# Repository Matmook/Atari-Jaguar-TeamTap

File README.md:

# Atari-Jaguar-TeamTap

This is an attempt to recreate the Atari Jaguar TeamTap schematic.

There is a catch on the original PCB: 
- the 5v from the Jaguar powers TeamTap's internal logic (74HC154 and 74HC244).
- pad's pin 7 is supposed to be used to power the pad's logic (74HC244).
- but all pads pin 7 are left floating in the TeamTam..
I guess that's some Atari magic => the pad's 74HC244 is fed by the other IOs, not VCC.
There is a "Magic" shunt on my pcb to test the pads behaviour when fed with 5v (as it should).

Matthieu Barreteau (Matmook) 2024

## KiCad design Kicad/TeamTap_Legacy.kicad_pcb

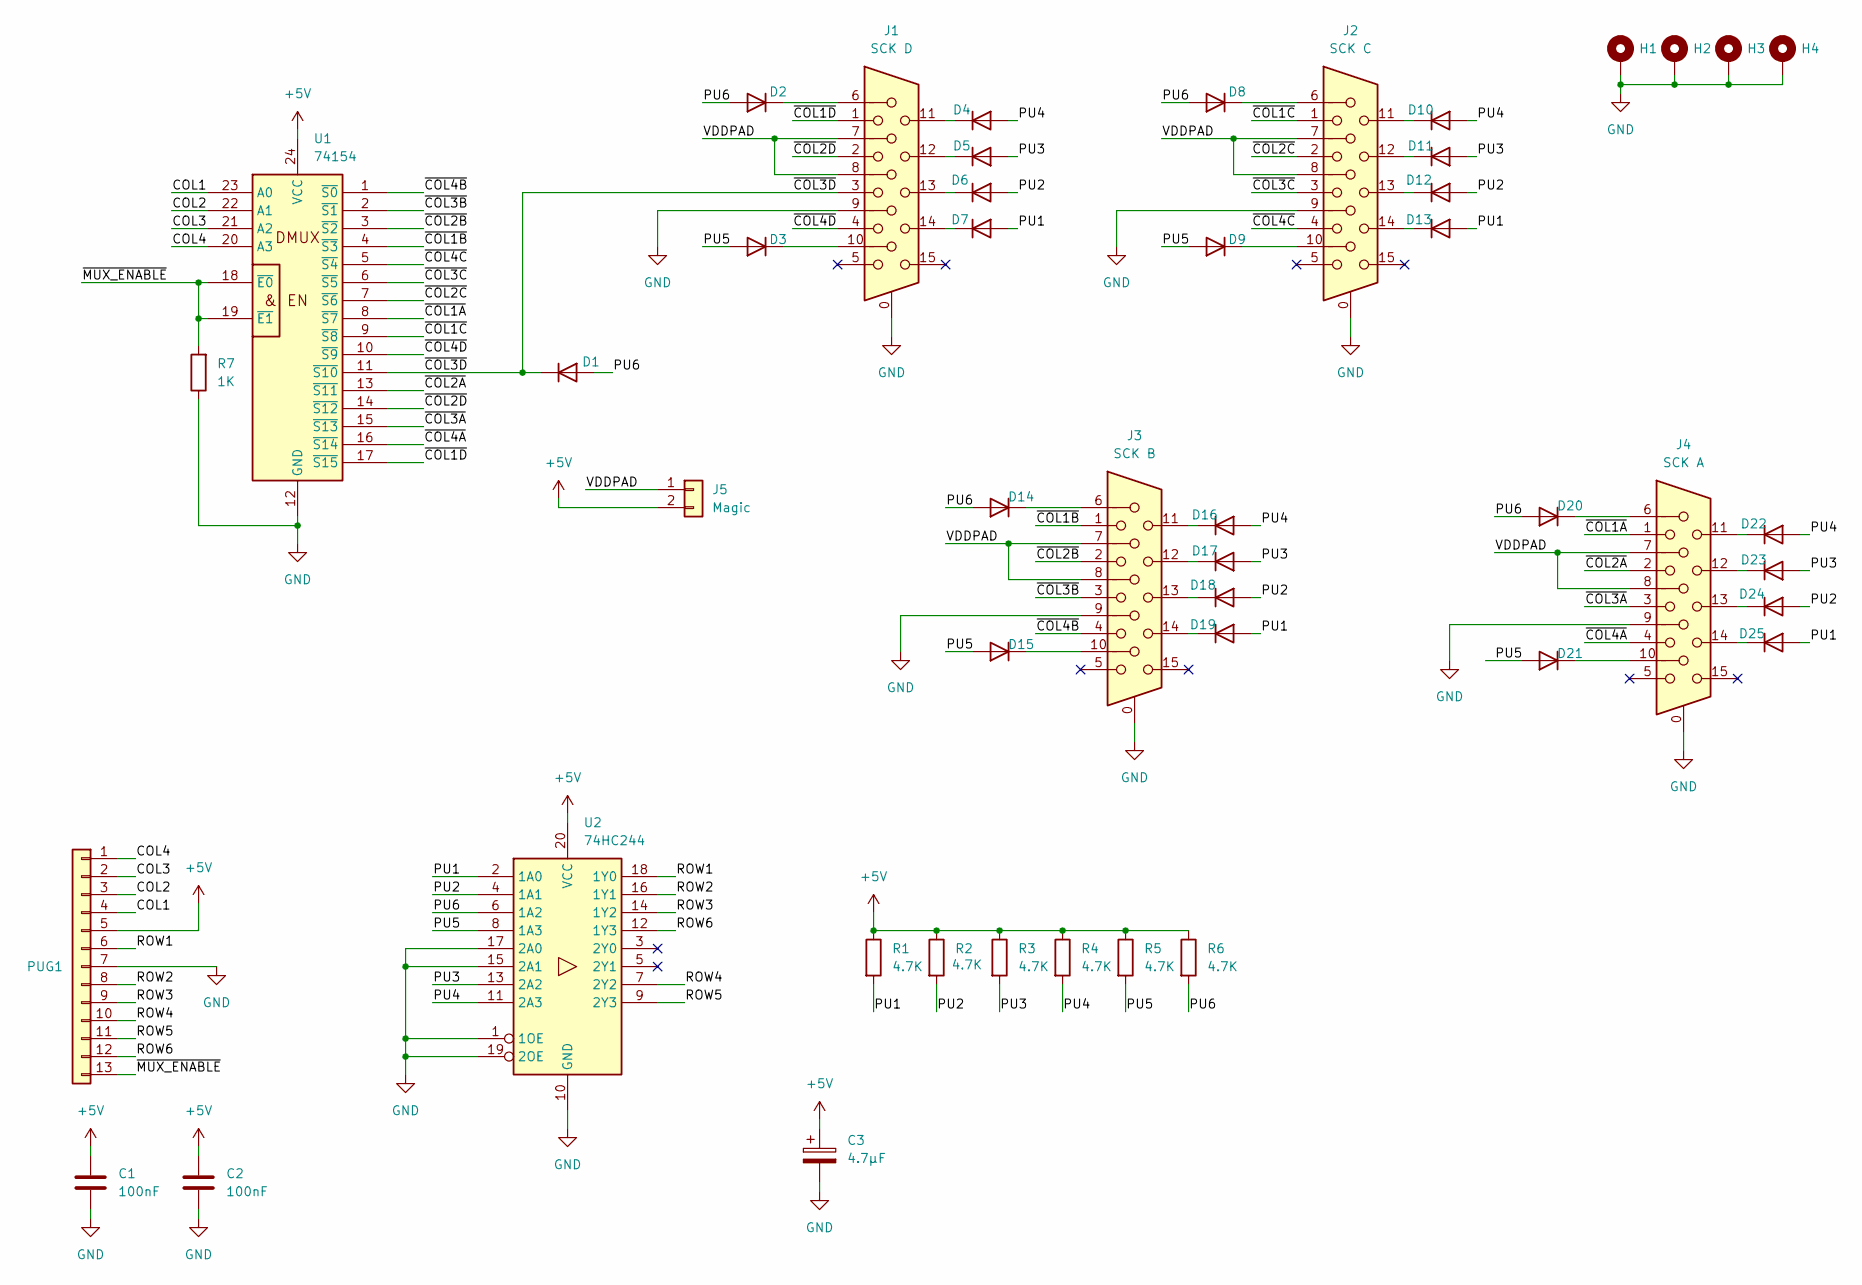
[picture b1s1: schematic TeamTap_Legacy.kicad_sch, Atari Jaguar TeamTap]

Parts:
C1, C2: 100nF; C_0603_1608Metric_Pad1.08x0.95mm_HandSolder
C3: 4.7µF; CP_Radial_D5.0mm_P2.50mm
D1, D2, D3, D4, D5, D6, D7, D8, D9, D10, D11, D12, D13, D14, D15, D16, D17, D18, D19, D20, D21, D22, D23, D24, D25: D; D_SOD-123
H1, H2, H3, H4: MountingHole_Pad; MountingHole_5mm_Pad_TopBottom
J1: SCK D; DSUB-15-HD_Male_Horizontal_P2.29x1.98mm_EdgePinOffset3.03mm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
J2: SCK C; DSUB-15-HD_Male_Horizontal_P2.29x1.98mm_EdgePinOffset3.03mm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
J3: SCK B; DSUB-15-HD_Male_Horizontal_P2.29x1.98mm_EdgePinOffset3.03mm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
J4: SCK A; DSUB-15-HD_Male_Horizontal_P2.29x1.98mm_EdgePinOffset3.03mm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
J5: Magic; PinHeader_1x02_P2.54mm_Vertical
PUG1: Conn_01x13; PinHeader_1x13_P2.54mm_Vertical
R1, R2, R3, R4, R5, R6: 4.7K; R_0603_1608Metric_Pad0.98x0.95mm_HandSolder
R7: 1K; R_0603_1608Metric_Pad0.98x0.95mm_HandSolder
U1: 74154; SOIC-24W_7.5x15.4mm_P1.27mm
U2: 74HC244; SOIC-20W_7.5x12.8mm_P1.27mm

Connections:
+5V: C1.1, C2.1, C3.1, J5.2, PUG1.5, R1.1, R2.1, R3.1, R4.1, R5.1, R6.1, U1.24 (VCC), U2.20 (VCC)
/COL1: PUG1.4, U1.23 (A0)
/COL2: PUG1.3, U1.22 (A1)
/COL3: PUG1.2, U1.21 (A2)
/COL4: PUG1.1, U1.20 (A3)
/PU1: D7.2 (A), D13.2 (A), D19.2 (A), D25.2 (A), R1.2, U2.2 (1A0)
/PU2: D6.2 (A), D12.2 (A), D18.2 (A), D24.2 (A), R2.2, U2.4 (1A1)
/PU3: D5.2 (A), D11.2 (A), D17.2 (A), D23.2 (A), R3.2, U2.13 (2A2)
/PU4: D4.2 (A), D10.2 (A), D16.2 (A), D22.2 (A), R4.2, U2.11 (2A3)
/PU5: D3.2 (A), D9.2 (A), D15.2 (A), D21.2 (A), R5.2, U2.8 (1A3)
/PU6: D1.2 (A), D2.2 (A), D8.2 (A), D14.2 (A), D20.2 (A), R6.2, U2.6 (1A2)
/ROW1: PUG1.6, U2.18 (1Y0)
/ROW2: PUG1.8, U2.16 (1Y1)
/ROW3: PUG1.9, U2.14 (1Y2)
/ROW4: PUG1.10, U2.7 (2Y2)
/ROW5: PUG1.11, U2.9 (2Y3)
/ROW6: PUG1.12, U2.12 (1Y3)
/VDDPAD: J1.7, J1.8, J2.7, J2.8, J3.7, J3.8, J4.7, J4.8, J5.1
/~COL1A: J4.1, U1.8 (~S7)
/~COL1B: J3.1, U1.4 (~S3)
/~COL1C: J2.1, U1.9 (~S8)
/~COL1D: J1.1, U1.17 (~S15)
/~COL2A: J4.2, U1.13 (~S11)
/~COL2B: J3.2, U1.3 (~S2)
/~COL2C: J2.2, U1.7 (~S6)
/~COL2D: J1.2, U1.14 (~S12)
/~COL3A: J4.3, U1.15 (~S13)
/~COL3B: J3.3, U1.2 (~S1)
/~COL3C: J2.3, U1.6 (~S5)
/~COL3D: D1.1 (K), J1.3, U1.11 (~S10)
/~COL4A: J4.4, U1.16 (~S14)
/~COL4B: J3.4, U1.1 (~S0)
/~COL4C: J2.4, U1.5 (~S4)
/~COL4D: J1.4, U1.10 (~S9)
/~MUX_ENABLE: PUG1.13, R7.2, U1.18 (~E0), U1.19 (~E1)
GND: C1.2, C2.2, C3.2, H1.1, H2.1, H3.1, H4.1, J1.0, J1.9, J2.0, J2.9, J3.0, J3.9, J4.0, J4.9, PUG1.7, R7.1, U1.12 (GND), U2.1 (1OE), U2.10 (GND), U2.15 (2A1), U2.17 (2A0), U2.19 (2OE)
unnamed: D2.1 (K), J1.6
unnamed: D3.1 (K), J1.10
unnamed: D4.1 (K), J1.11
unnamed: D5.1 (K), J1.12
unnamed: D6.1 (K), J1.13
unnamed: D7.1 (K), J1.14
unnamed: D8.1 (K), J2.6
unnamed: D9.1 (K), J2.10
unnamed: D10.1 (K), J2.11
unnamed: D11.1 (K), J2.12
unnamed: D12.1 (K), J2.13
unnamed: D13.1 (K), J2.14
unnamed: D14.1 (K), J3.6
unnamed: D15.1 (K), J3.10
unnamed: D16.1 (K), J3.11
unnamed: D17.1 (K), J3.12
unnamed: D18.1 (K), J3.13
unnamed: D19.1 (K), J3.14
unnamed: D20.1 (K), J4.6
unnamed: D21.1 (K), J4.10
unnamed: D22.1 (K), J4.11
unnamed: D23.1 (K), J4.12
unnamed: D24.1 (K), J4.13
unnamed: D25.1 (K), J4.14

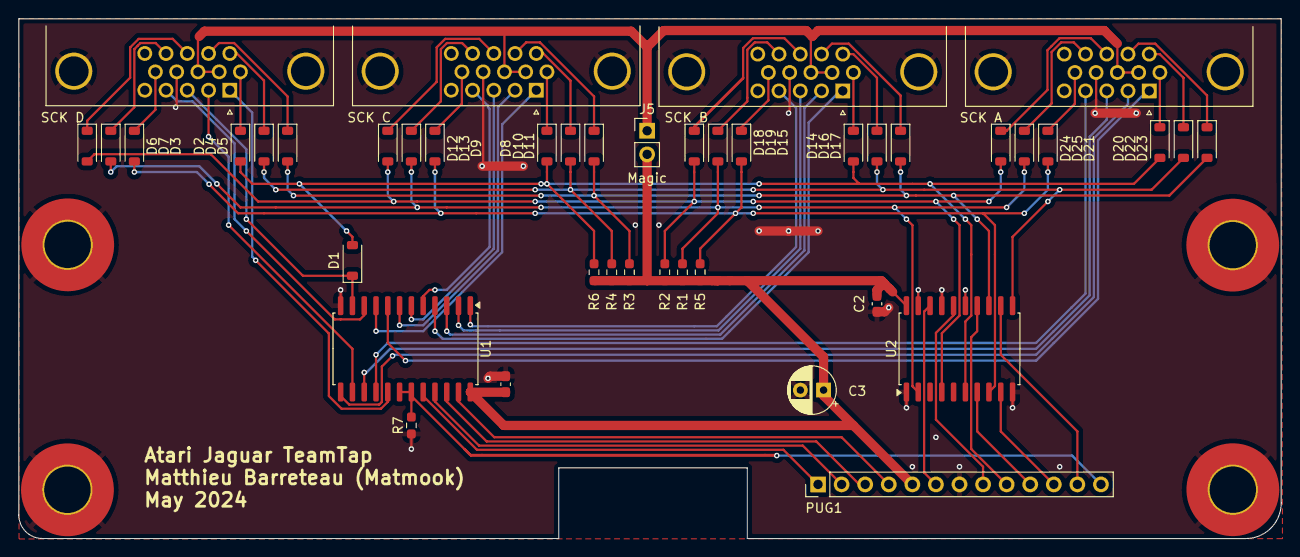
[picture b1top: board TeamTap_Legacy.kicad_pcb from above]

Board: 2 copper layers, 136.0 x 56.0 mm, 47 parts (0 on the bottom side), 60 nets.

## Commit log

2024-05-05 Atari Jaguar TeamTap schematic
2024-05-05 Cleaning
2024-09-08 Screenshots added
